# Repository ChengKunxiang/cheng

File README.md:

# cheng
To reinforce each line,need heat shrink tubings or adhesive tapes.
To connect each part,need breadboard and dupont Lines

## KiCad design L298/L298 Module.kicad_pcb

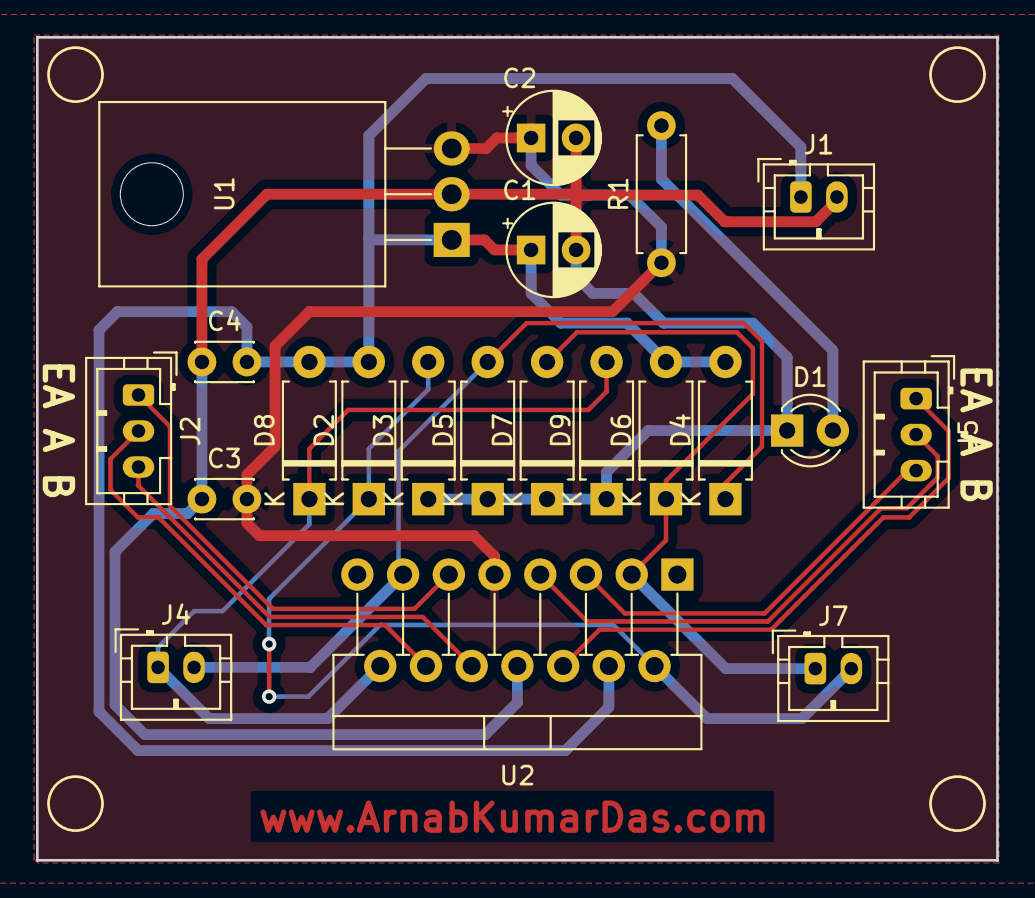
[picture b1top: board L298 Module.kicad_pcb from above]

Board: 2 copper layers, 53.3 x 45.7 mm, 21 parts (0 on the bottom side), 14 nets.

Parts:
C1, C2: 47u; CP_Radial_D5.0mm_P2.50mm
C3, C4: 100n; C_Disc_D3.0mm_W2.0mm_P2.50mm
D1: LED; LED_D3.0mm
D2, D3, D4, D5, D6, D7, D8, D9: 1N4007; D_A-405_P7.62mm_Horizontal
J1: POWER; JST_PH_B2B-PH-K_1x02_P2.00mm_Vertical
J2: MOTOR2 IN; JST_PH_B3B-PH-K_1x03_P2.00mm_Vertical
J4: MOTOR2 OUT; JST_PH_B2B-PH-K_1x02_P2.00mm_Vertical
J5: MOTOR1 IN; JST_PH_B3B-PH-K_1x03_P2.00mm_Vertical
J7: MOTOR1 OUT; JST_PH_B2B-PH-K_1x02_P2.00mm_Vertical
R1: R; R_Axial_DIN0207_L6.3mm_D2.5mm_P7.62mm_Horizontal
U1: L7805; TO-220-3_Horizontal_TabDown
U2: L298HN; TO-220-15_P2.54x2.54mm_StaggerOdd_Lead4.58mm_Vertical

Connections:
+5V: C2.1, C3.2, R1.1, U1.3 (OUT), U2.9 (Vss)
+BATT: C1.1, C4.2, D2.2 (A), D4.2 (A), D6.2 (A), D8.2 (A), J1.1, U1.1 (IN), U2.4 (Vs)
GND: C1.2, C2.2, C3.1, C4.1, D1.1 (K), D3.1 (K), D5.1 (K), D7.1 (K), D9.1 (K), J1.2, U1.2 (GND), U2.8 (GND)
unnamed: D1.2 (A), R1.2
unnamed: D2.1 (K), D3.2 (A), J7.2, U2.2 (OUT1)
unnamed: D4.1 (K), D5.2 (A), J4.2, U2.13 (OUT3)
unnamed: D6.1 (K), D7.2 (A), J7.1, U2.3 (OUT2)
unnamed: D8.1 (K), D9.2 (A), J4.1, U2.14 (OUT4)
unnamed: J2.1, U2.11 (EnB)
unnamed: J2.2, U2.12 (IN4)
unnamed: J2.3, U2.10 (IN3)
unnamed: J5.1, U2.6 (EnA)
unnamed: J5.2, U2.7 (IN2)
unnamed: J5.3, U2.5 (IN1)

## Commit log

2023-11-21 Add files via upload
    symbolic circuit of the mobile platform
2023-11-25 Add files via upload
    this is test code
